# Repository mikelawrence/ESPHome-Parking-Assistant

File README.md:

# ESPHome Parking Assistant

From early on I learned that parking the car in the garage was a problem the needed to be solved. My Dad solved his problem with a piece of styrofoam hanging from the ceiling. When it touched the windshield you knew to stop. This was very important because the lawn mowing equipment was in front of the car. Crunch time was inevitable, don't ask me how I know. 

I recently moved and the problem became an issue again. Not because there was a crunch time incident but because we needed as much room as possible in front of the car. Having to get out of the car multiple times to make sure the door won't hit the car was a pain. So I did some searching on Youtube and found this [video](https://www.youtube.com/watch?v=HqqlY4_3kQ8) from ResinChem Tech. I really liked his use of a RGB LED strip to indicate position and when to stop. There is a ton of information so watch the whole video.1

***So yes this project is a complete ripoff of his idea!*** But I wanted to do several things different. First I wanted to use ESPHome. Second I really like designing my own hardware. And third I want to keep learning how to use Fusion 360 to design 3D printed stuff.

## Design Decisions

### ESP32 and ESPHome

ESPHome is closely aligned with Home Assistant. In fact they are the same company. Home Assistant uses ESPHome for some of their hardware like the [Home Assistant Voice Preview Edition](https://www.home-assistant.io/voice-pe/) or [Bluetooth Proxy](https://esphome.io/components/bluetooth_proxy.html). I chose a newer ESP32-S3 for this design which also has Bluetooth support. The newer ESP32's work better with the ESP-IDF framework as opposed to the default Arduino framework. Not everything is supported in the ESP-IDF, particularly several of the RGB LED libraries but the ESP32 RMT LED Strip library works well once you make sure have enough RMT memory allocated.

### USB-C Power Delivery

I liked the idea of using RGB LED Pixels since ESPHome supports these directly without custom code. I wanted a flexible power supply for driving the RGB LED Pixels both in the power capacity and voltage. I've been using a MagWLED driver for driving RGB LED pixels for a while now and I really like it's approach to using USB-C PD (Power Delivery) to select between 5V and 12V. The USB-C PD 2.0/3.0 specification supports currents greater than 3A but will need a USB-C Power Cable with E-Marker and a USB-C PD Power Source that supports these higher currents. I went with the simpler and more supported max 3A. The USB-C PD 2.0/3.0 specification will negotiate several fixed voltages at 3A: 5V-15W, 9V-27W, 12V-36W, 15V-45W and 20V-60W. 12V-36W PD is less common in chargers but 9V-27W is always available. 12V RGB LED Pixels will usually run on 9V, the difference in LED brightness is not that noticeable and may make your LED live longer. To handle the USB-C PD negotiation I chose the STUSB4500 from ST Microelectronics. This guy will support negotiate all of the USB-C PD 2.0/3.0 specification but this design will support only the following: 5V-15W, 9V-27W or 12V-36W. The STUSB4500 will be configured to support 12V-36W with a fallback of 9V-27W or just 5V-15W

The STUSB45000 will negotiate 20V by default if the USB-C PD Power Source supports it so our power supplies must support an input voltage range of 5V - 20V. The STUSB4500 uses an external pass transistor to enable V<sub>BUS</sub> at higher currents and voltages when PD is properly negotiated. Until the configured PD is properly negotiated this pass transistor is turned off. Using USB-C PD to provide a variable input voltage from USB-C PD is elegant but if 9V-27W or 12V-36W PD is configured 3.3V is still needed for the ESP32 and 5V for the TFMini. This means two DC/DC converters are necessary, one 3.3V @ 600mA to support primarily the ESP32-S3 chip and 5V @ 1.0A primarily for the TFMini Plus sensor. 

The 3.3V power supply will always have an input voltage greater than 3.3V. I could use a linear regulator but I wanted to get more experience designing efficient DC/DC converters so I chose the TPS560430 SIMPLE SWITCHER® 4-V to 36-V, 600-mA Synchronous Step-Down Converter. The 3.3V power supply is connected directly to the USB connector and will power the ESP32-S3 immediately. If you connect this board to a older USB 2.0 power source you may only get 5V at 500mA. This is enough to get the ESP32-S3 running without violating the 500mA max requirement.

For the 5V @ 1A power supply it's input voltage can be 5V so a regular step-down will not work. I chose the TPS552872, 36-V, 4-A, Fully Integrated Buck-boost Converter also from TI. This converter will switch to boost mode when the input voltage is 5V and still operate correctly. This power supply must be connected to the V<sub>BUS</sub> pass transistor and not directly to the V<sub>BUS</sub> on the USB connector. Doing so would exceed the 500mA maximum when connected to a USB 2.0 power source. Some USB 2.0 Power Sources support more than 500mA but the specification states 500mA maximum. So until PD is properly negotiated the V<sub>BUS</sub> to the RGB LED pixels and the 5.V power supply are not enabled.

An INA228 85-V, 20-Bit, Ultra-Precise Power/Energy/Charge Monitor With I2C Interface device is used to monitor both energy and power consumption. Energy consumption is a better metric than instantaneous power for understanding actual device usage. Just look at what the power company uses to bill you (kWh).

### TFMini Plus

ResinChem Tech compared multiple distance sensors in his video. He settled on the TFMini-S sensor. I also chose a TFMini sensor but went with the TFMini Plus because it was in a more durable package with a lens cover. The spot size is different but in my tests this sensor worked just fine. This sensor can use a UART or I2C interface. The default UART interface can be set to automatically send measurements at a specified rate while the I2C must be setup with a UART command first and requires polling. The TFMini Plus requires 5V power but uses 3.3V logic levels.

### RGB LED pixel interface

This board only supports RGB LED pixels that have a single data line for communication. SPI pixels are NOT supported. RGB LED pixels requires 5V logic level on the data and while many will tell you that it will work just fine with 3.3V logic I prefer to be more conservative. After doing some [research](https://electricfiredesign.com/2021/03/12/logic-level-shifters-for-driving-led-strips/) I chose the TC4427V MOSFET Driver. It can source/sink 1.5A; definatley help long cable runs. Note the V temperature range option. The V option does more that expand the temperature range it also lowers V<sub>IH</sub> from 2.4V to 2.0V. This give plenty of margin for 3.3V ESP32 with a worst case V<sub>OH</sub> of 0.8\*VCC or 0.8\*3.0=2.4V.

## Enclosure

The enclosure is designed to mount on [Elfa](https://www.containerstore.com/s/elfa/garage-plus-by-elfa/garage-plus-by-elfa-predesigned-spaces/garage-plus-7-tier-6-wall-shelving-solution/123d?productId=11023646) wire shelving. I used [Autodesk Fusion](https://www.autodesk.com/products/fusion-360/overview) to design this enclosure. I'm a novice with this tool but I'm always looking to improve. For this design I tried out a few new features of Fusion, namely Rendering and Animation.

<p align="center">
     <br />
    Exploded View of Enclosure
</p>

## PCB

This 4-layer board is designed with [KiCad](https://www.kicad.org/). I been using this free tool for a while and it just keeps getting better and better.

<p align="center">
     <br />
    3D Render of ESPHome Parking Assistant PCB
</p>

## Operation

### LED status

There are six LEDs on the PCB to indicate status.

* **Status:** If dark something is misconfigured or damaged. If blue PS was successfully negotiated. If Power Delivery failed but +5V is available on VBUS the LED will be red. Generally you shouldn't be using the connected power brick for lighting up the LEDs unless you know it can support the power requirements. Keep in mind this board was designed for USB-C Power Delivery so why don't you connect one.
* **+5V:** Will be green when the +5V power supply is on. This power supply comes from VBUS and supports 4.5V - 22 V inputs.
* **+3.3V:** Will be green when the +3.3V power supply is on. This power supply is always on when connected to USB-C or USB 2.0 power sources. If the LED is off then the USB is not connected or there is a failure.
* **PD5V:** Will be blue when PDO1 (+5V) has been negotiated.
* **PD9V:** Will be blue when PDO2 (+9V) has been negotiated.
* **PD12V:** Will be blue when PDO3 (+12V) has been negotiated.

> [!NOTE]
> Only one of the three PD LEDs will be lit at a time. 

### Connecting RGB LED strips

The mate to the on-board terminal strip connector is Phoenix Contact 1847071.

The LED connector has 4 wires.

* **PD**: This is the LED voltage wire, often labeled 12V+ or 5V. This PCB supports up to 3A at 5V, 9V or 12V as long as the correct USB-C PD Power Source is connected.
* **33Ω**: This is data line with a 33Ω series resistor. Use this for longer wire runs over 10ft.
* **249Ω**: This is the same data line but with a 249Ω series resistor. Use this for shorter wire runs.
* **GND**: This is minus side of the LED voltage.

> [!NOTE]
> Connect only one of 33Ω or 249Ω to your LED Strip.
> [!NOTE]
> Many 12V RGB LEDs run just fine on 9V. In fact running at 9V may extend their life expectancy.

## Configuration

### STUSB4500 Configuration

> [!CAUTION]
> When configuring the STUSB4500 for the first time you should realize its default configuration will allow up to 20V on V<sub>BUS</sub>. This PCB works fine with 20V but this voltage is passed to the LED connector. Make sure your LEDs are disconnected before configuring the STUSB4500.

1. Uncomment either the 12V LED section or the 5V LED section in the ```config.yaml``` file.
2. Uncomment ```flash_nvm: true``` in the ```config.yaml``` file
   You should see the following messages in your log.

     ```log
     [00:10:03][C][stusb4500:112]: STUSB4500:
     [00:10:03][E][stusb4500:119]:   NVM has been flashed, power cycle the device to reload NVM
     ```

   If you forgot to uncomment ```flash_nvm: true``` to the configuration you will see an error in the log.

     ```log
     [00:06:27][C][stusb4500:112]: STUSB4500:
     [00:06:27][E][stusb4500:114]:   NVM does not match current settings, you should set flash_nvm: true for one boot
     [00:06:27][C][stusb4500:130]:   PDO3 negotiated 20.00V @ 1.00A, 20.00W
     ```

3. Power cycle your board. Make sure ```NVM matches settings``` is present in the log and that one of your PDOs was negotiated. The example below shows the result of the 12V LED configuration.

   ```log
   [00:00:19][C][stusb4500:112]: STUSB4500:
   [00:00:19][C][stusb4500:116]:   NVM matches settings
   [00:00:19][C][stusb4500:130]:   PDO3 negotiated 12.00V @ 3.00A, 36.00W
   ```

4. If you selected the 12V LED config section you should see either the PD12V LED or PD9V LED lit. PD5V should be lit if you selected the 5V LED section. 

5. The STUSB4500 component does check to see that the NVM is indeed different before flashing the NVM but it is prudent to remove the ```NVM matches settings``` after it is clear the STUSB4500 is working as intended. You don't want to wear out your NVM.

### Installation

Place the enclosure so the the sensor hits as flat an area as possible. For my car this is the license plate. You may have to play different options for best performance. My experience was pretty much place and forget. It just

Now the sensor is placed, close the garage door with no car present. Home Assistant will show the measured distance. Convert to cm if necessary and subtract half of ```door_tolerance``` set ```door_distance``` to this value.

Next we set ```start_distance``` to ```door_distance``` - 25 and install the current config.

For the final setting, open the garage door and park your car where you want it. Set ```stop_distance``` using the converted distance, if necessary, from Home Assistant and again install the current config.

You now have a basic setup. Testing is in order. Back the car first and then start moving back in. Watch the LED strip light turn on and start movig toward the center as you move the car in. Stop as soon as the LED strip light turn green. Check the parking position and adjust ```stop_distance``` a little bit. As you repeat this test you will get a feel for how much to change ```stop_distance``` to get the car to stop in the right place.

## Status

* PCB Rev B: Fabricated by JLCPCB and tested. The 5V DC/DC converter issues for Rev A are resolved. This board is fully operational.
* PCB Rev A: Fabricated by JLCPCB and tested. Worked well enough to write the code for ESPHome including the new STB4500 and TFMini components. The main problem with Rev A was the 5V DC/DC converter won't start at 5V. This was technically in the datasheet but there was also a minimum operating voltage the was well below 5V input. I didn't realize that you need to apply more than 5V for the regulator to start working and then you can lower the input to 5V. Not exactly what I needed.
* Enclosure: Printed and successfully tested on Rev A. Rev B has been fully tested.

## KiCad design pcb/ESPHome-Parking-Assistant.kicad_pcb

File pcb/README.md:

# ESPHome Parking Assistant PCB
<p align="center">
     <br />
</p>

The PCB is designed in [KiCad](https://www.kicad.org/). Fabrication and Assembly is tuned toward [JCLPCB](https://jlcpcb.com/). The production folder has everything you need for JLCPCB to send you fully assembled boards.

## Schematic
<p align="center">
     <br />
</p>

### Do Not Populate (DNP) Notes
* ```C9```, ```C10```, ```R16``` and ```R17```: These components are an optional snubber used to reduce EMI. Not needed.
* ```R31``` and ```R32``` are pullups for open drain outputs. If these pins are used the 10K pullup will be enabled on the ESP32 input pins.
* ```R33``` and ```R35``` are pullups for the I<sub>2</sub>C Bus. By default the internal ESP32 pullups are enabled.
* ```R34``` and ```R36``` can be used to pullup or pulldown the ```CONFIG``` pin on the TFLuna connector. For now this is not necessary because the code only supports the UART interface on the TFLuna and leaving ```CONFIG``` floating will enable the UART. 
* ```R26``` is used to compensate for cable droop. Not currently used.

## Bill of Materials
<p align="center">
     <br />
    Interactive BOM
</p>

## PCB Info
* 4 layer to support an additional ground plane and signal layer to reduce plane interruptions on the outer layers.
* Dimension are 85mm X 59mm.
* Requires oven reflow or hot air to assemble some components.
* Supports TFMini Plus, TFMini-S and TFLuna Range Finder Sensors. Enclosure is designed for TFMini Plus Sensor.

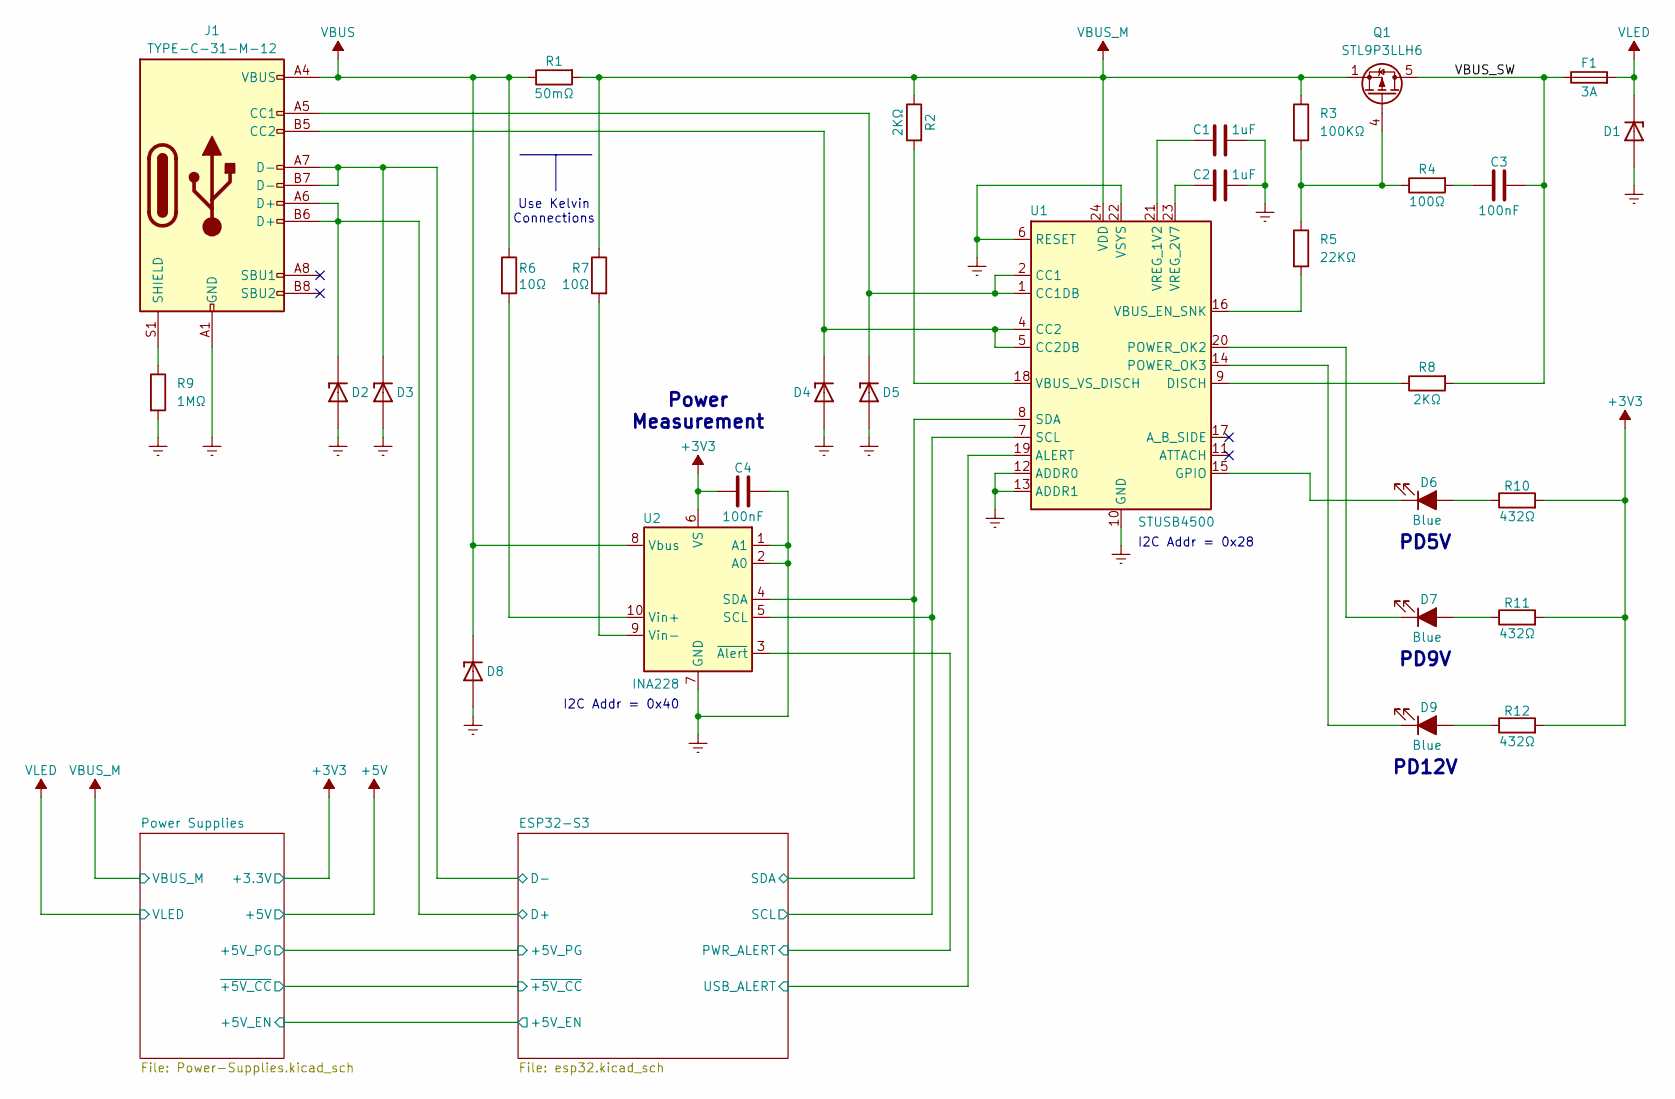
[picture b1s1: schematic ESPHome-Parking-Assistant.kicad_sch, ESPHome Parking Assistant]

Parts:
C1, C2: 1uF; C_0603_1608Metric; Part Number CL10A105KB8NNNC; LCSC C15849
C3, C4: 100nF; C_0402_1005Metric; Part Number CL05B104KB54PNC; LCSC C307331
D1, D4, D5, D8: ESDA25P35-1U1M; TVS_ESDA25P35-1U1M; Part Number ESDA25P35-1U1M; LCSC C1974707
D2, D3: ESDA7P60-1U1M; TVS_ESDA25P35-1U1M; Part Number ESDA7P60-1U1M; LCSC C1975146
D6, D7, D9: Blue; LED_0603_1608Metric; Part Number F.0603.00026/P2-0603B1TS2-06T-001; LCSC C7496819
F1: 3A; Fuse_1812_4532Metric; LCSC C2760295
J1: TYPE-C-31-M-12; USB_C_Receptacle_HRO_TYPE-C-31-M-12; Part Number TYPE-C-31-M-12; LCSC C165948
Q1: STL9P3LLH6; TRANS_STL9P3LLH6; Part Number STL9P3LLH6; LCSC C2969828
R1: 50mΩ; R_2512_6332Metric; LCSC C375690
R2, R8: 2KΩ; R_0402_1005Metric; LCSC C4109
R3: 100KΩ; R_0402_1005Metric; LCSC C25741
R4: 100Ω; R_0402_1005Metric; LCSC C25076
R5: 22KΩ; R_0402_1005Metric; LCSC C25768
R6, R7: 10Ω; R_0402_1005Metric; LCSC C25077
R9: 1MΩ; R_0402_1005Metric; LCSC C26083
R10, R11, R12: 432Ω; R_0402_1005Metric; LCSC C25113
U1: STUSB4500; QFN-24-1EP_4x4mm_P0.5mm_EP2.7x2.7mm; Part Number STUSB4500QTR; LCSC C2678061
U2: INA228; VSSOP-10_3x3mm_P0.5mm; Part Number INA228AIDGSR; LCSC C2887910

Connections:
+3V3: C4.2, R10.2, R11.2, R12.2, U2.6 (VS); also elsewhere on the board
/ESP32-S3/D+: D2.C, J1.A6 (D+), J1.B6 (D+); also elsewhere on the board
/ESP32-S3/D-: D3.C, J1.A7 (D-), J1.B7 (D-); also elsewhere on the board
/ESP32-S3/PWR_ALERT: U2.3 (~Alert); also elsewhere on the board
/ESP32-S3/SCL: U1.7 (SCL), U2.5 (SCL); also elsewhere on the board
/ESP32-S3/SDA: U1.8 (SDA), U2.4 (SDA); also elsewhere on the board
/ESP32-S3/USB_ALERT: U1.19 (ALERT); also elsewhere on the board
/VBUS_SW: C3.2, F1.1, Q1.5 (D), R8.2
GND: C1.1, C2.1, C4.1, D1.A, D2.A, D3.A, D4.A, D5.A, D8.A, J1.A1 (GND), J1.A12 (GND), J1.B1 (GND), J1.B12 (GND), R9.2, U1.6 (RESET), U1.10 (GND), U1.12 (ADDR0), U1.13 (ADDR1), U1.22 (VSYS), U1.25 (GND), U2.1 (A1), U2.2 (A0), U2.7 (GND); also elsewhere on the board
unnamed: C3.1, R4.2
unnamed: D6.2 (A), R10.1
unnamed: D6.1 (K), U1.15 (GPIO)
unnamed: D7.2 (A), R11.1
unnamed: D7.1 (K), U1.20 (POWER_OK2)
unnamed: D9.2 (A), R12.1
unnamed: D9.1 (K), U1.14 (POWER_OK3)
unnamed: D5.C, J1.A5 (CC1), U1.1 (CC1DB), U1.2 (CC1)
unnamed: D4.C, J1.B5 (CC2), U1.4 (CC2), U1.5 (CC2DB)
unnamed: J1.S1 (SHIELD), R9.1
unnamed: Q1.4 (G), R3.2, R4.1, R5.1
unnamed: R8.1, U1.9 (DISCH)
unnamed: R5.2, U1.16 (VBUS_EN_SNK)
unnamed: R2.2, U1.18 (VBUS_VS_DISCH)
unnamed: C1.2, U1.21 (VREG_1V2)
unnamed: C2.2, U1.23 (VREG_2V7)
unnamed: R6.2, U2.10 (Vin+)
unnamed: R7.2, U2.9 (Vin-)
VBUS: D8.C, J1.A4 (VBUS), J1.A9 (VBUS), J1.B4 (VBUS), J1.B9 (VBUS), R1.1, R6.1, U2.8 (Vbus)
VBUS_M: Q1.1 (S), Q1.2 (S), Q1.3 (S), R1.2, R2.1, R3.1, R7.1, U1.24 (VDD); also elsewhere on the board
VLED: D1.C, F1.2; also elsewhere on the board

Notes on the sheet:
PD9V
I2C Addr = 0x40
Use Kelvin Connections
PD5V
PD12V
Power Measurement
I2C Addr = 0x28

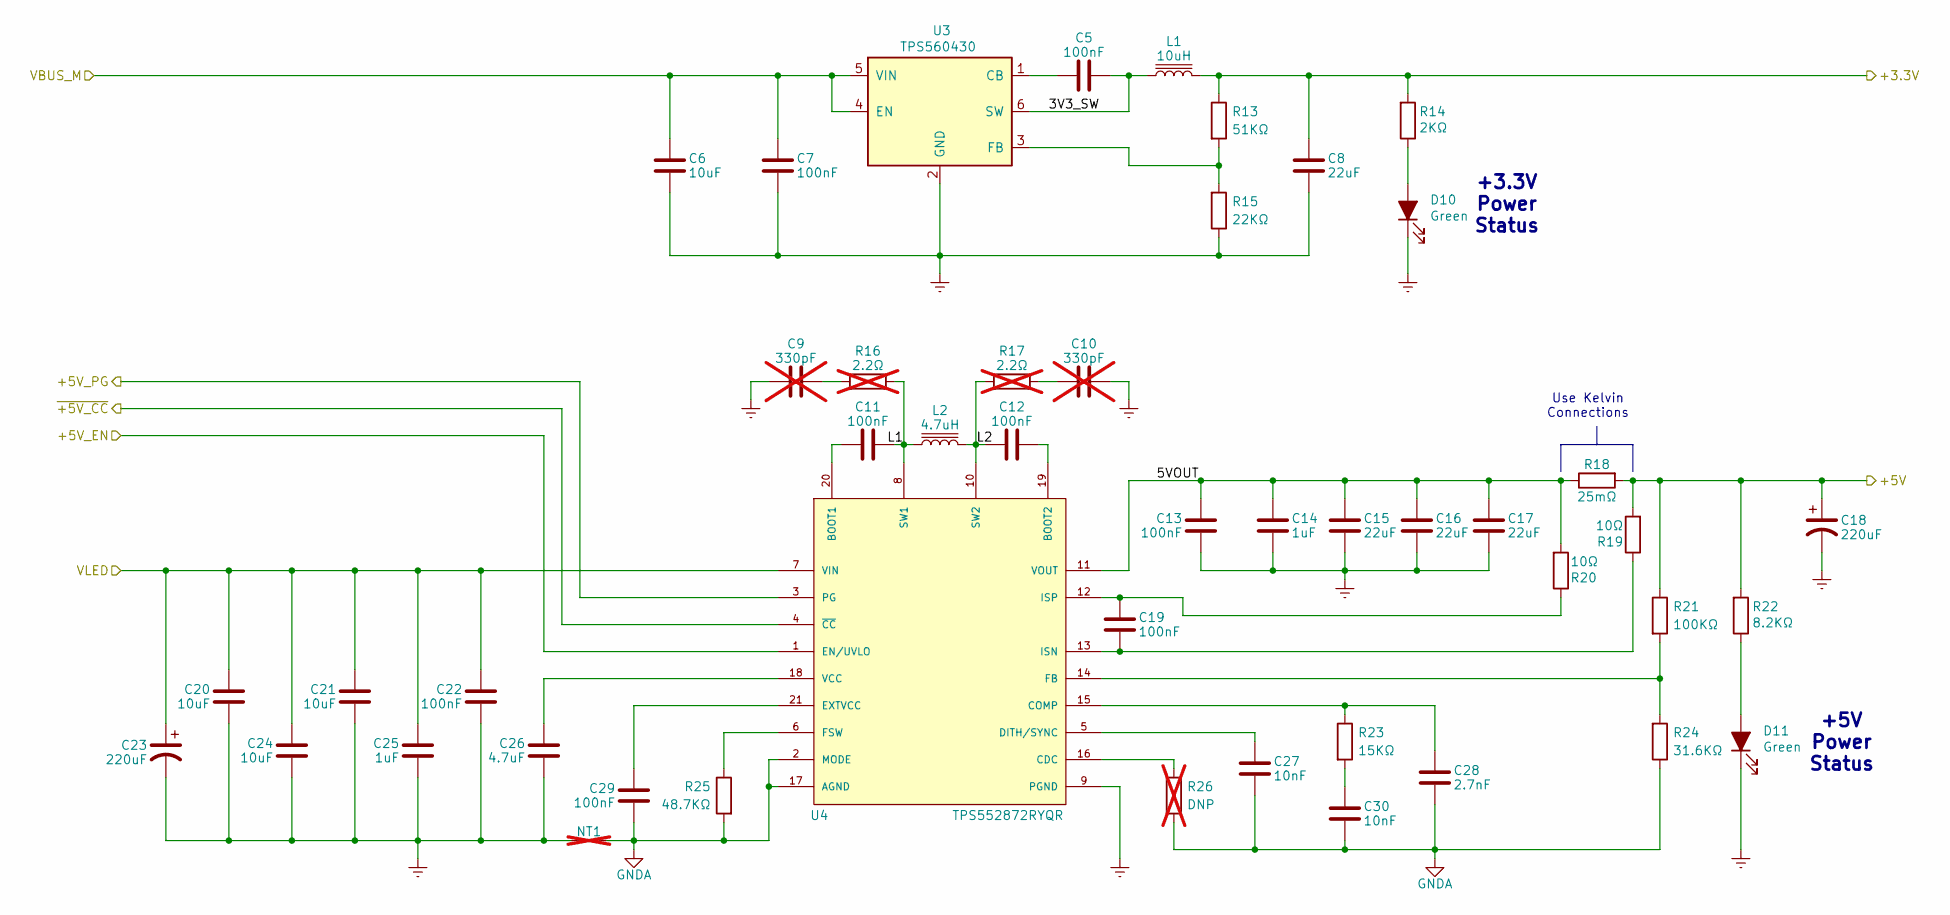
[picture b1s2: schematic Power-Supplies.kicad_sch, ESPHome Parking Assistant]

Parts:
C5, C7, C11, C12, C13, C19, C22, C29: 100nF; C_0402_1005Metric; Part Number CL05B104KB54PNC; LCSC C307331
C6, C20, C21, C24: 10uF; C_1206_3216Metric; Part Number CL31A106KBHNNNE; LCSC C13585
C8, C15, C16, C17: 22uF; C_0805_2012Metric; Part Number LMK212BJ226MG-T; LCSC C92814
C9, C10: 330pF; C_1206_3216Metric; Part Number CC1206JRNPO9BN331; LCSC C541477; not fitted
C14, C25: 1uF; C_0603_1608Metric; Part Number CL10A105KB8NNNC; LCSC C15849
C18, C23: 220uF; CP_Elec_8x10.5; Part Number EEEFK1V221P; LCSC C178562
C26: 4.7uF; C_0603_1608Metric; Part Number CL10A475KO8NNNC; LCSC C19666
C27, C30: 10nF; C_0402_1005Metric; Part Number CL05B103KB5NNNC; LCSC C15195
C28: 2.7nF; C_0402_1005Metric; Part Number CL05B272KB5NNNC; LCSC C84704
D10, D11: Green; LED_0603_1608Metric; Part Number F.0603.00025/P2-0603G1TS2-06T-002; LCSC C7496818
L1: 10uH; IND_VLCF4028T-100M1R0-2; Part Number VLCF4028T-100M1R0-2; LCSC C694593
L2: 4.7uH; L_Vishay_IHLP-2020; Part Number IHLP2020CZER4R7M11; LCSC C845007
NT1: NetTie-2_SMD_Pad0.5mm; not fitted
R13: 51KΩ; R_0402_1005Metric; LCSC C25794
R14: 2KΩ; R_0402_1005Metric; LCSC C4109
R15: 22KΩ; R_0402_1005Metric; LCSC C25768
R16, R17: 2.2Ω; R_1206_3216Metric; LCSC C104742; not fitted
R18: 25mΩ; R_0805_2012Metric; LCSC C2767472
R19, R20: 10Ω; R_0402_1005Metric; LCSC C25077
R21: 100KΩ; R_0402_1005Metric; LCSC C25741
R22: 8.2KΩ; R_0402_1005Metric; LCSC C36953
R23: 15KΩ; R_0402_1005Metric; LCSC C25539
R24: 31.6KΩ; R_0402_1005Metric; LCSC C226989
R25: 48.7KΩ; R_0402_1005Metric; LCSC C26981
R26: DNP; R_0402_1005Metric; not fitted
U3: TPS560430; SOT-23-6; Part Number TPS560430XDBVR; LCSC C524782
U4: TPS552872RYQR; VQFN21_RYQ_TEX; Part Number TPS552872RYQR; LCSC C22397842

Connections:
+3V3: C8.2, L1.2, R13.1, R14.2; also elsewhere on the board
+5V: C18.1, R18.2, R19.2, R21.1, R22.2; also elsewhere on the board
/ESP32-S3/+5V_EN: U4.1 (EN/UVLO); also elsewhere on the board
/ESP32-S3/+5V_PG: U4.3 (PG); also elsewhere on the board
/ESP32-S3/~+5V_CC: U4.4 (~CC); also elsewhere on the board
/Power Supplies/3V3_SW: C5.2, L1.1, U3.6 (SW)
/Power Supplies/5VOUT: C13.2, C14.1, C15.2, C16.2, C17.2, R18.1, R20.2, U4.11 (VOUT)
/Power Supplies/L1: C11.2, L2.1, R16.1, U4.8 (SW1)
/Power Supplies/L2: C12.1, L2.2, R17.2, U4.10 (SW2)
GND: C6.2, C7.1, C8.1, C9.1, C10.2, C13.1, C14.2, C15.1, C16.1, C17.1, C18.2, C20.2, C21.2, C22.1, C23.2, C24.2, C25.2, C26.1, D10.1 (K), D11.1 (K), NT1.1, R15.1, U3.2 (GND), U4.9 (PGND); also elsewhere on the board
GNDA: C27.1, C28.1, C29.1, C30.1, NT1.2, R24.1, R25.2, R26.2, U4.2 (MODE), U4.17 (AGND)
unnamed: C9.2, R16.2
unnamed: C10.1, R17.1
unnamed: C30.2, R23.2
unnamed: D10.2 (A), R14.1
unnamed: D11.2 (A), R22.1
unnamed: C5.1, U3.1 (CB)
unnamed: R13.2, R15.2, U3.3 (FB)
unnamed: C11.1, U4.20 (BOOT1)
unnamed: C12.2, U4.19 (BOOT2)
unnamed: R26.1, U4.16 (CDC)
unnamed: C28.2, R23.1, U4.15 (COMP)
unnamed: C27.2, U4.5 (DITH/SYNC)
unnamed: C29.2, U4.21 (EXTVCC)
unnamed: R21.2, R24.2, U4.14 (FB)
unnamed: R25.1, U4.6 (FSW)
unnamed: C19.1, R19.1, U4.13 (ISN)
unnamed: C19.2, R20.1, U4.12 (ISP)
unnamed: C26.2, U4.18 (VCC)
VBUS_M: C6.1, C7.2, U3.4 (EN), U3.5 (VIN); also elsewhere on the board
VLED: C20.1, C21.1, C22.2, C23.1, C24.1, C25.1, U4.7 (VIN); also elsewhere on the board

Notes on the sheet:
+5V Power Status
+3.3V Power Status
Use Kelvin Connections

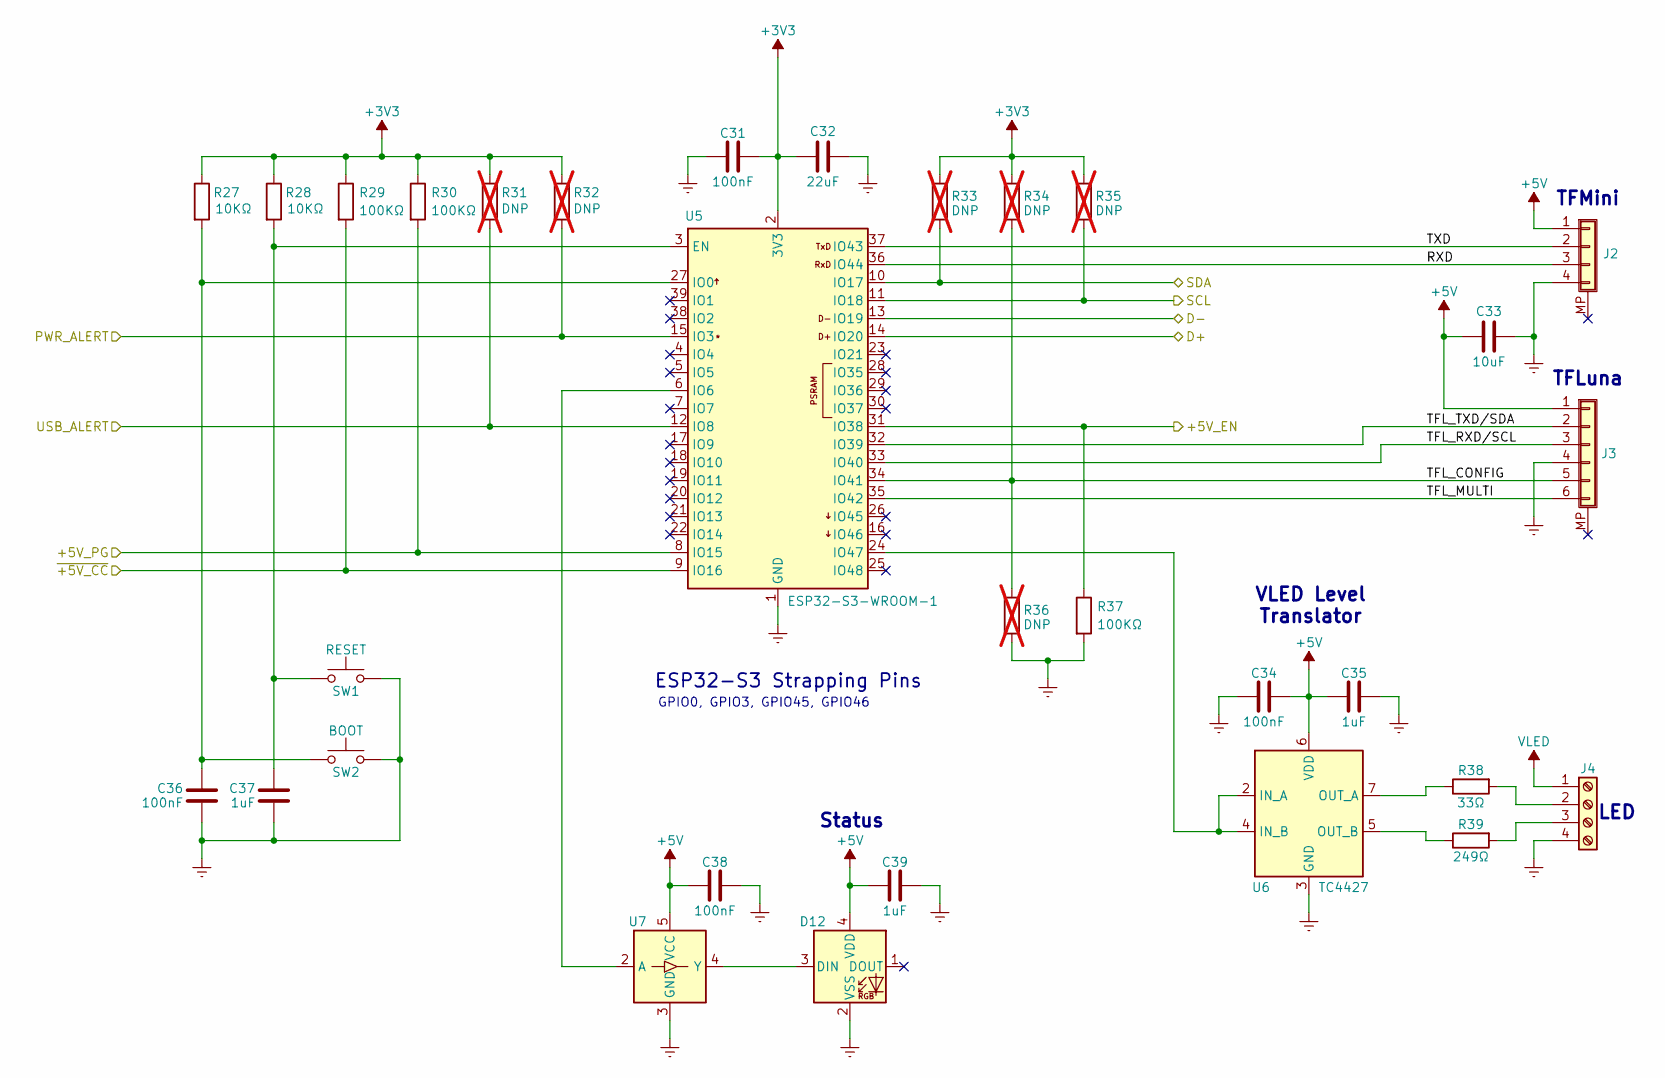
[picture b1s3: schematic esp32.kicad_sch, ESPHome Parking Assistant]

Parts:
C31, C34, C36, C38: 100nF; C_0402_1005Metric; Part Number CL05B104KB54PNC; LCSC C307331
C32: 22uF; C_0805_2012Metric; Part Number LMK212BJ226MG-T; LCSC C92814
C33: 10uF; C_1206_3216Metric; Part Number CL31A106KBHNNNE; LCSC C13585
C35, C37, C39: 1uF; C_0603_1608Metric; Part Number CL10A105KB8NNNC; LCSC C15849
D12: WS2812B-2020; LED_WS2812B-2020_PLCC4_2.0x2.0mm; Part Number WS2812B-2020; LCSC C965555
J2: 533980471; Molex_PicoBlade_53398-0471_1x04-1MP_P1.25mm_Vertical; Part Number 533980471; LCSC C17617036
J3: 533980671; Molex_PicoBlade_53398-0671_1x06-1MP_P1.25mm_Vertical; Part Number 533980671; LCSC C277393
J4: Screw_Terminal_01x04; PhoenixContact_MC_1,5_4-GF-3.5_1x04_P3.50mm_Horizontal_Thre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; Part Number 1843813
R27, R28: 10KΩ; R_0402_1005Metric; LCSC C25531
R29, R30, R37: 100KΩ; R_0402_1005Metric; LCSC C25741
R31, R32, R33, R34, R35, R36: DNP; R_0402_1005Metric; not fitted
R38: 33Ω; R_1210_3225Metric; LCSC C105005
R39: 249Ω; R_1210_3225Metric; LCSC C874850
SW1: RESET; SW_SPST_B3U-1000P-B; Part Number B3U-1000P; LCSC C231329
SW2: BOOT; SW_SPST_B3U-1000P-B; Part Number B3U-1000P; LCSC C231329
U5: ESP32-S3-WROOM-1; Part Number ESP32-S3-WROOM-1-N8R8; LCSC C2913201
U6: TC4427; SOIC-8_3.9x4.9mm_P1.27mm; Part Number TC4427VOA; LCSC C636893
U7: SN74LV1T34DBV; SOT-23-5; Part Number SN74LV1T34DBV; LCSC C100024

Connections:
+3V3: C31.2, C32.1, R27.1, R28.1, R29.1, R30.1, R31.1, R32.1, R33.1, R34.1, R35.1, U5.2 (3V3); also elsewhere on the board
+5V: C33.1, C34.2, C35.2, C38.1, C39.1, D12.4 (VDD), J2.1, J3.1, U6.6 (VDD), U7.5 (VCC); also elsewhere on the board
/ESP32-S3/+5V_EN: R37.1, U5.31 (IO38); also elsewhere on the board
/ESP32-S3/+5V_PG: R30.2, U5.8 (IO15); also elsewhere on the board
/ESP32-S3/D+: U5.14 (IO20); also elsewhere on the board
/ESP32-S3/D-: U5.13 (IO19); also elsewhere on the board
/ESP32-S3/PWR_ALERT: R32.2, U5.15 (IO3); also elsewhere on the board
/ESP32-S3/RXD: J2.3, U5.36 (IO44)
/ESP32-S3/SCL: R35.2, U5.11 (IO18); also elsewhere on the board
/ESP32-S3/SDA: R33.2, U5.10 (IO17); also elsewhere on the board
/ESP32-S3/TFL_CONFIG: J3.5, R34.2, R36.1, U5.34 (IO41)
/ESP32-S3/TFL_MULTI: J3.6, U5.35 (IO42)
/ESP32-S3/TFL_RXD/SCL: J3.3, U5.33 (IO40)
/ESP32-S3/TFL_TXD/SDA: J3.2, U5.32 (IO39)
/ESP32-S3/TXD: J2.2, U5.37 (IO43)
/ESP32-S3/USB_ALERT: R31.2, U5.12 (IO8); also elsewhere on the board
/ESP32-S3/~+5V_CC: R29.2, U5.9 (IO16); also elsewhere on the board
GND: C31.1, C32.2, C33.2, C34.1, C35.1, C36.1, C37.2, C38.2, C39.2, D12.2 (VSS), J2.4, J3.4, J4.4, R36.2, R37.2, SW1.1, SW2.1, U5.1 (GND), U5.40 (GND), U5.41 (GND), U6.3 (GND), U7.3 (GND); also elsewhere on the board
unnamed: D12.3 (DIN), U7.4 (Y)
unnamed: J4.2, R38.2
unnamed: J4.3, R39.2
unnamed: C37.1, R28.2, SW1.2, U5.3 (EN)
unnamed: C36.2, R27.2, SW2.2, U5.27 (IO0)
unnamed: U5.6 (IO6), U7.2 (A)
unnamed: U5.24 (IO47), U6.2 (IN_A), U6.4 (IN_B)
unnamed: R38.1, U6.7 (OUT_A)
unnamed: R39.1, U6.5 (OUT_B)
VLED: J4.1; also elsewhere on the board

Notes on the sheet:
LED
GPIO0, GPIO3, GPIO45, GPIO46
TFLuna
TFMini
VLED Level Translator
ESP32-S3 Strapping Pins
Status

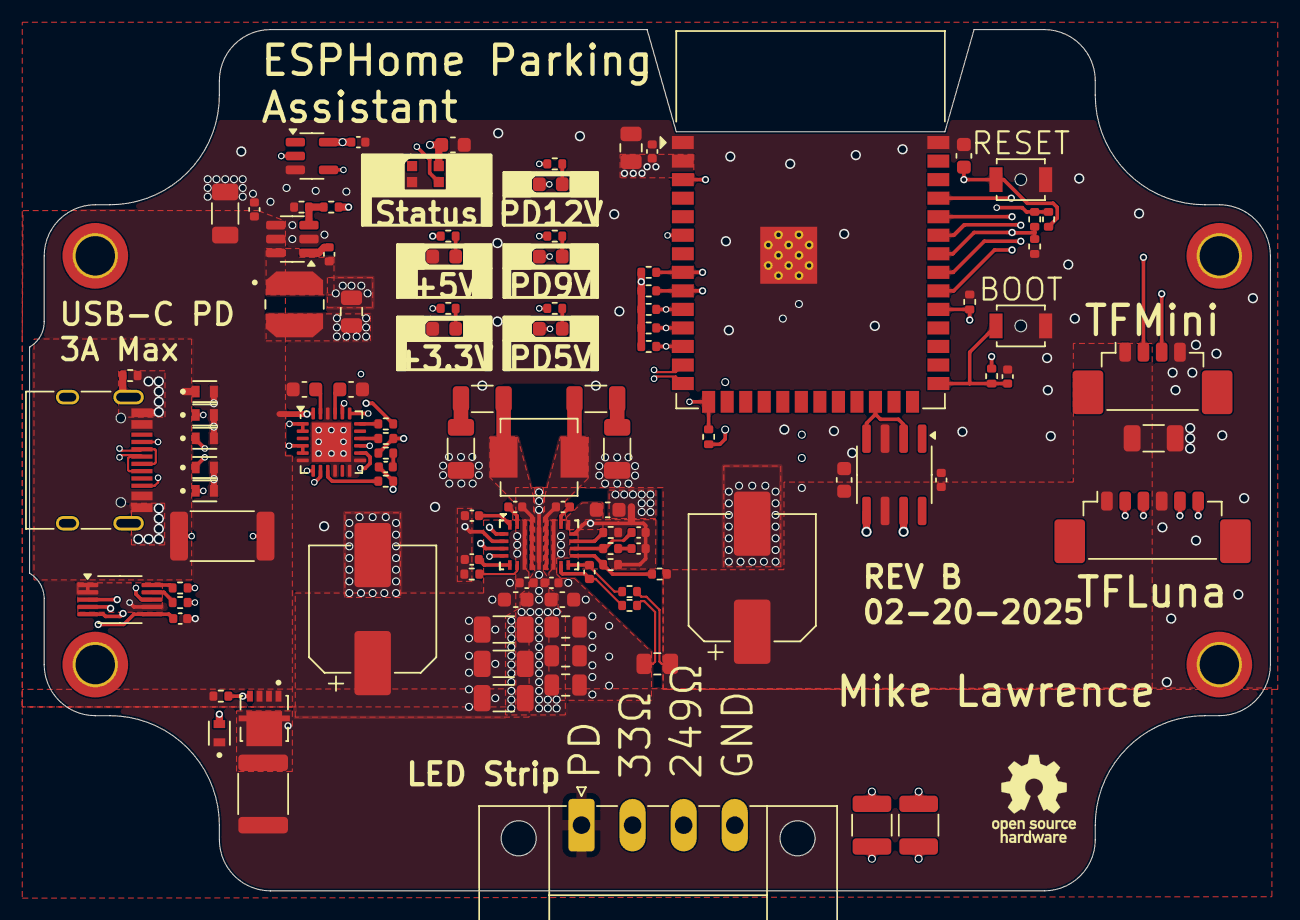
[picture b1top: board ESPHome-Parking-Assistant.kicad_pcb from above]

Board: 4 copper layers, 85.0 x 59.0 mm, 114 parts (1 on the bottom side), 72 nets.

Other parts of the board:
MH1, MH2, MH3, MH4: MountingHole_2.7mm_M2.5_ISO7380_Pad_TopBottom
TEXT1: OSHW-Logo_5.7x6mm_SilkScreen
TEXT2: OSHW-Logo2_24.3x20mm_SilkScreen

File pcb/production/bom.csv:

Designator,Footprint,Quantity,Value,LCSC Part #
"C1, C14, C2, C25, C35, C37, C39",0603,7,1uF,C15849
"C11, C12, C13, C19, C22, C29, C3, C31, C34, C36, C38, C4, C5, C7",0402,14,100nF,C307331
"C15, C16, C17, C32, C8",0805,5,22uF,C92814
"C18, C23",CP_Elec_8x10.5,2,220uF,C178562
"C20, C21, C24, C33, C6",1206,5,10uF,C13585
C26,0603,1,4.7uF,C19666
"C27, C30",0402,2,10nF,C15195
C28,0402,1,2.7nF,C84704
"D1, D4, D5, D8",TVS_ESDA25P35-1U1M,4,ESDA25P35-1U1M,C1974707
"D10, D11",0603,2,Green,C7496818
D12,LED_WS2812B-2020_PLCC4_2.0x2.0mm,1,WS2812B-2020,C965555
"D2, D3",TVS_ESDA25P35-1U1M,2,ESDA7P60-1U1M,C1975146
"D6, D7, D9",0603,3,Blue,C7496819
F1,1812,1,3A,C2760295
J1,USB_C_Receptacle_HRO_TYPE-C-31-M-12,1,TYPE-C-31-M-12,C165948
J2,Molex_PicoBlade_53398-0471_1x04-1MP_P1.25mm_Vertical,1,533980471,C17617036
J3,Molex_PicoBlade_53398-0671_1x06-1MP_P1.25mm_Vertical,1,533980671,C277393
J4,"PhoenixContact_MC_1,5_4-GF-3.5_1x04_P3.50mm_Horizontal_ThreadedFlange_MountHole",1,Screw_Terminal_01x04,
L1,IND_VLCF4028T-100M1R0-2,1,10uH,C694593
L2,L_Vishay_IHLP-2020,1,4.7uH,C845007 
Q1,TRANS_STL9P3LLH6,1,STL9P3LLH6,C2969828
R1,2512,1,50mΩ,C375690
"R10, R11, R12",0402,3,432Ω,C25113
R13,0402,1,51KΩ,C25794
"R14, R2, R8",0402,3,2KΩ,C4109
"R15, R5",0402,2,22KΩ,C25768
R18,0805,1,25mΩ,C2767472
"R19, R20, R6, R7",0402,4,10Ω,C25077
"R21, R29, R3, R30, R37",0402,5,100KΩ,C25741
R22,0402,1,8.2KΩ,C36953
R23,0402,1,15KΩ,C25539
R24,0402,1,31.6KΩ,C226989
R25,0402,1,48.7KΩ,C26981
"R27, R28",0402,2,10KΩ,C25531
R38,1210,1,33Ω,C105005
R39,1210,1,249Ω,C874850
R4,0402,1,100Ω,C25076
R9,0402,1,1MΩ,C26083
SW1,SW_SPST_B3U-1000P-B,1,RESET,C231329
SW2,SW_SPST_B3U-1000P-B,1,BOOT,C231329
U1,QFN-24-1EP_4x4mm_P0.5mm_EP2.7x2.7mm,1,STUSB4500,C2678061
U2,VSSOP-10_3x3mm_P0.5mm,1,INA228,C2887910
U3,SOT-23-6,1,TPS560430,C524782
U4,VQFN21_RYQ_TEX,1,TPS552872RYQR,C22397842
U5,ESP32-S3-WROOM-1,1,ESP32-S3-WROOM-1,C2913201
U6,SOIC-8_3.9x4.9mm_P1.27mm,1,TC4427,C636893
U7,SOT-23-5,1,SN74LV1T34DBV,C100024

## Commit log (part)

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2025-02-22 Just beginning the commit process. More to come soon.
2025-02-22 README editing
2025-02-22 Add section READMEs and the ESPHome config.yaml
2025-02-22 Fix README links
2025-02-23 Move components to new repository
2025-02-23 Edit README.
    Remove lck file
2025-02-23 Improving READMEs
2025-02-23 Fix broken link
2025-02-23 Fix broken link.
    Repair Caption alignment
2025-02-23 Further README refinement.
    Changes to config.yaml to support new README information.
2025-02-23 Add PCB section and edit Enclosure section
2025-02-23 Revert "Add PCB section and edit Enclosure section"
    This reverts commit f3cafefe5a9607d9db253730a9622a0c797a1213.
2025-02-24 Update README.md
    Grammar fixes and readability edits
2025-02-25 Add note about Homer Assistant Garage Door Sensor and how to remove if you don't have it.
2025-02-25 More README cleanup.
2025-02-25 Change R23 to 15KΩ
2025-02-25 Fix last commit. R26 is DNP and R23 changed to 15kΩ.
2025-02-25 Add link to schematic in pdf form and some notes about the schematic.
2025-02-25 Update README.md
    Make PCB image larger
2025-02-25 Add PCB STL file
2025-03-04 Fixed incorrectly marked Status LEDs on PCB.
    New notes on LED status in README.
    Updated config.yaml based on more testing in the lab.
2025-04-11 Update interactive BOM and README.
